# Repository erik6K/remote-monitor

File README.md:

# Repeater Monitor
## Background
An IoT device has been created to monitor the 240V AC normal supply, and 12V DC battery back-up supply for a radio repeater. Refer to the Project Design and Testing Document submitted along with this git repository for more information. The purpose of this git repository is to:
* Store the Arduino firmware backups for deploying new devices, or adding functionality
* Store relevent hardware manuals

To facilitate continuous deployment of the web application, it has been moved to a separate git repository. Updates to the web application should be made within this repository: [Repeater Monitor Web Application](https://github.com/tarrantja/remote-monitor-web). Updates made to the web application contained within this repository will not be deployed. 

## Authors
Created by:
* **Rio Akbar** (22507035)
* **Calvin Nguyen** (22509815)
* **Erik Stefan** (22224939)
* **James Tarrant** (20924309)
* **Dylan Turner** (22240231)

Developed for use in CITS3200, on behalf of SES CSU. 
[The full git repository can be found here.](https://github.com/tarrantja/remote-monitor-web)

## Licences
Hardware: CC BY-NC 3.0 AU

Firmware: GPLv3

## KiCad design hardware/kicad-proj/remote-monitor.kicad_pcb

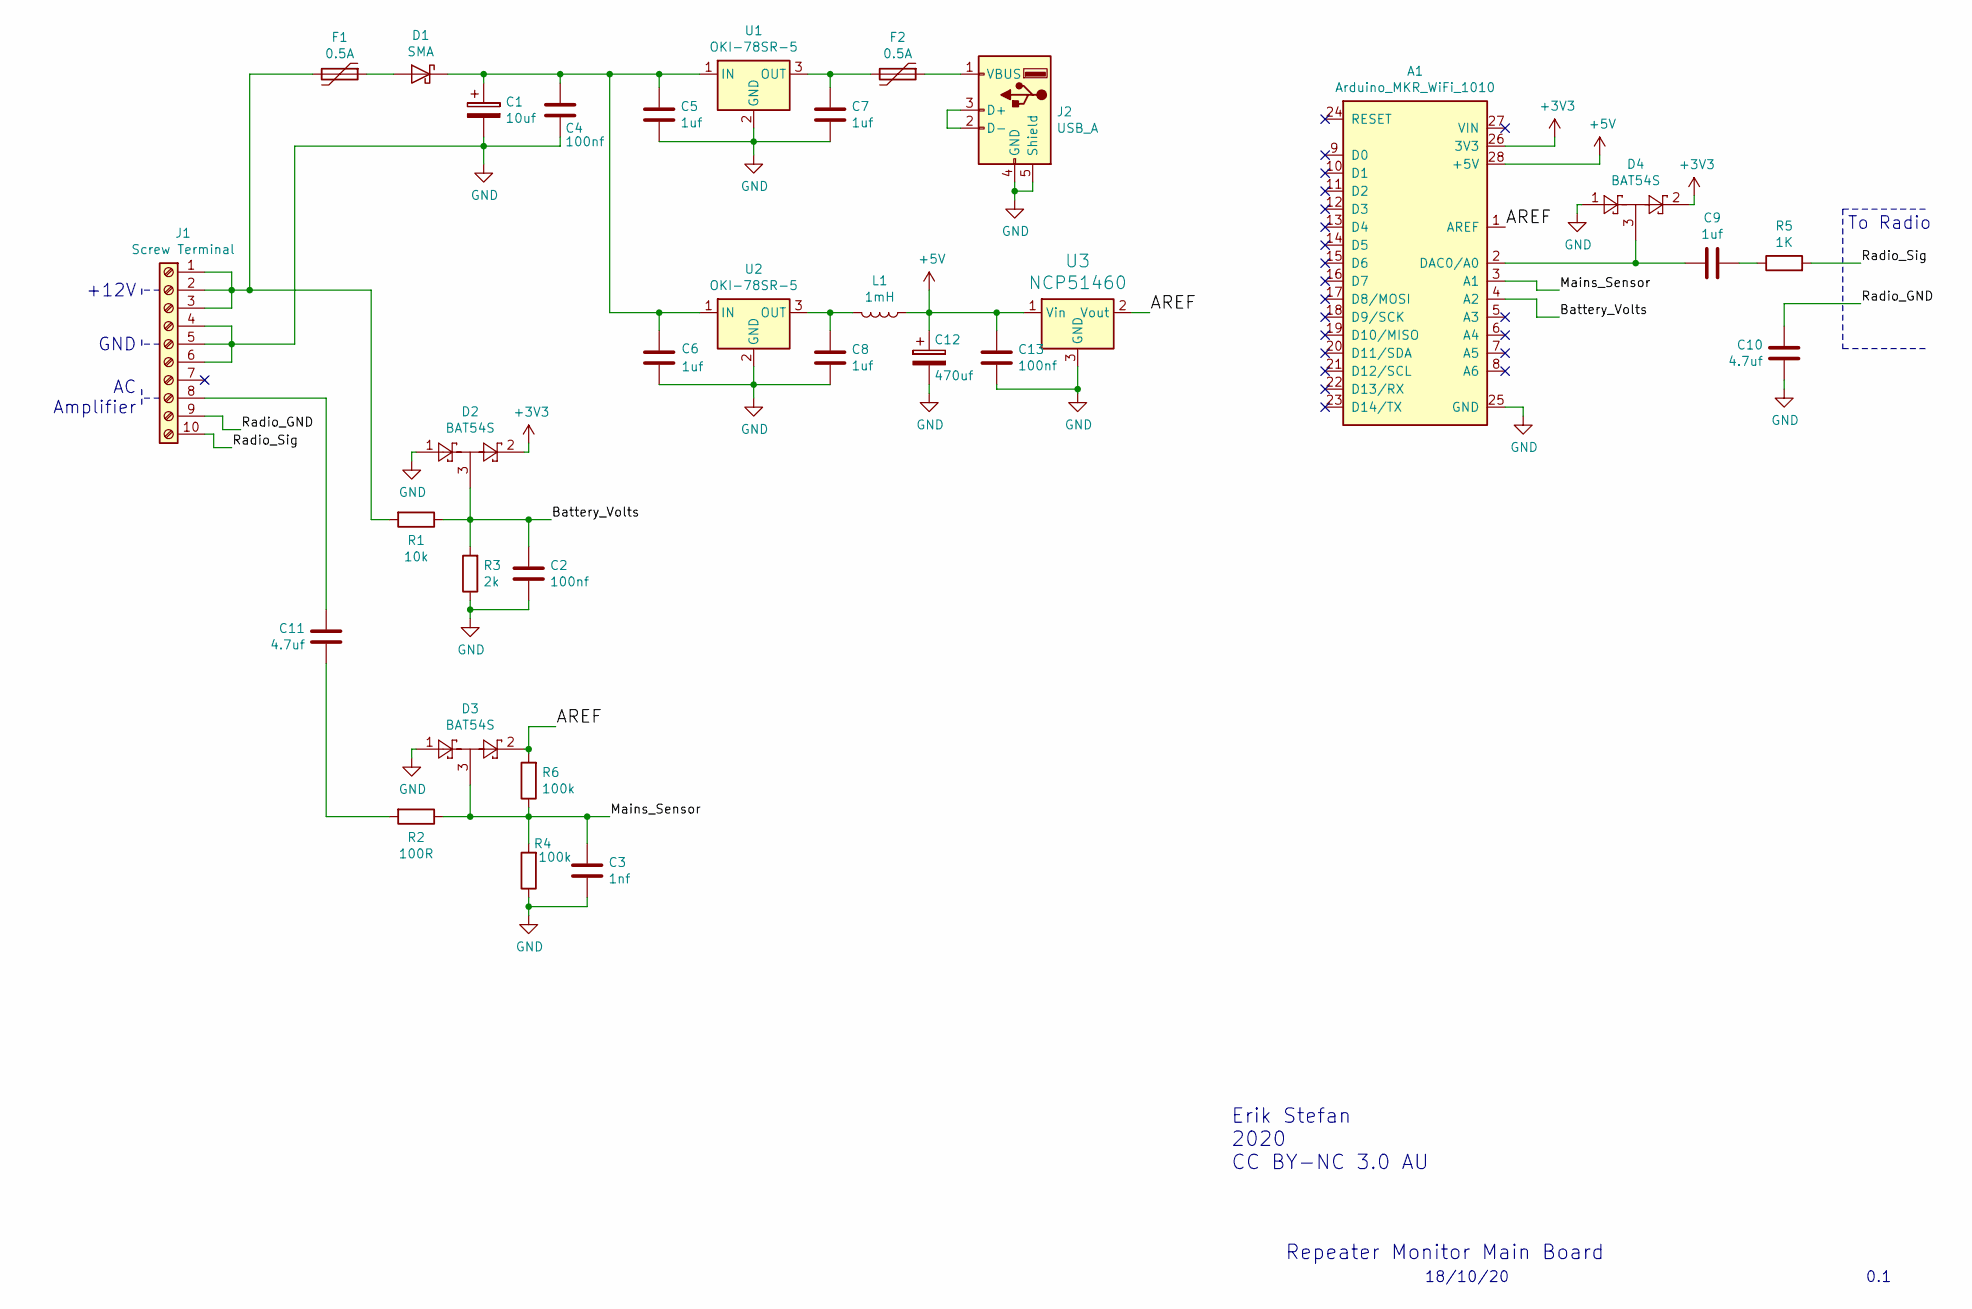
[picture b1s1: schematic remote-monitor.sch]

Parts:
A1: Arduino_MKR_WiFi_1010; Arduino_MKR_1010
C1: 10uf; CP_Elec_5x4.5
C2, C4, C13: 100nf; C_1206_3216Metric
C3: 1nf; C_1206_3216Metric
C5, C6, C7, C8, C9: 1uf; C_1206_3216Metric
C10, C11: 4.7uf; C_1206_3216Metric
C12: 470uf; CP_Elec_8x10.5
D1: SMA; D_SMA
D2, D3, D4: BAT54S; SOT-23
F1, F2: 0.5A; Fuse_1812_4532Metric
J1: Screw Terminal; Screw_Terminal_1x10
J2: USB_A; USB_A_Molex_105057_Vertical
L1: 1mH; L_6.3x6.3_H3
R1: 10k; R_1206_3216Metric
R2: 100R; R_1206_3216Metric
R3: 2k; R_1206_3216Metric
R4, R6: 100k; R_1206_3216Metric
R5: 1K; R_1206_3216Metric
U1, U2: OKI-78SR-5; Converter_DCDC_muRata_OKI-78SR_Vertical
U3: NCP51460; SOT-23

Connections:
+3V3: A1.26 (3V3), D2.2, D4.2
+5V: A1.28 (+5V), C12.1, C13.1, L1.1, U3.1 (Vin)
/AREF: A1.1 (AREF), D3.2, R6.2, U3.2 (Vout)
/Battery_Volts: A1.4 (A2), C2.1, D2.3, R1.1, R3.2
/Mains_Sensor: A1.3 (A1), C3.1, D3.3, R2.1, R4.2, R6.1
/Radio_GND: C10.1, J1.9
/Radio_Sig: J1.10, R5.2
GND: A1.25 (GND), C1.2, C2.2, C3.2, C4.2, C5.2, C6.2, C7.2, C8.2, C10.2, C12.2, C13.2, D2.1, D3.1, D4.1, J1.4, J1.5, J1.6, J2.4 (GND), J2.5 (Shield), R3.1, R4.1, U1.2 (GND), U2.2 (GND), U3.3 (GND)
unnamed: A1.2 (DAC0/A0), C9.2, D4.3
unnamed: C1.1, C4.1, C5.1, C6.1, D1.1 (K), U1.1 (IN), U2.1 (IN)
unnamed: C7.1, F2.2, U1.3 (OUT)
unnamed: C8.1, L1.2, U2.3 (OUT)
unnamed: C9.1, R5.1
unnamed: C11.1, J1.8
unnamed: C11.2, R2.2
unnamed: D1.2 (A), F1.1
unnamed: F1.2, J1.1, J1.2, J1.3, R1.2
unnamed: F2.1, J2.1 (VBUS)
unnamed: J2.2 (D-), J2.3 (D+)

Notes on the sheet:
0.1
Repeater Monitor Main Board
Erik Stefan 2020 CC BY-NC 3.0 AU
18/10/20
+12V
GND
AC Amplifier
To Radio

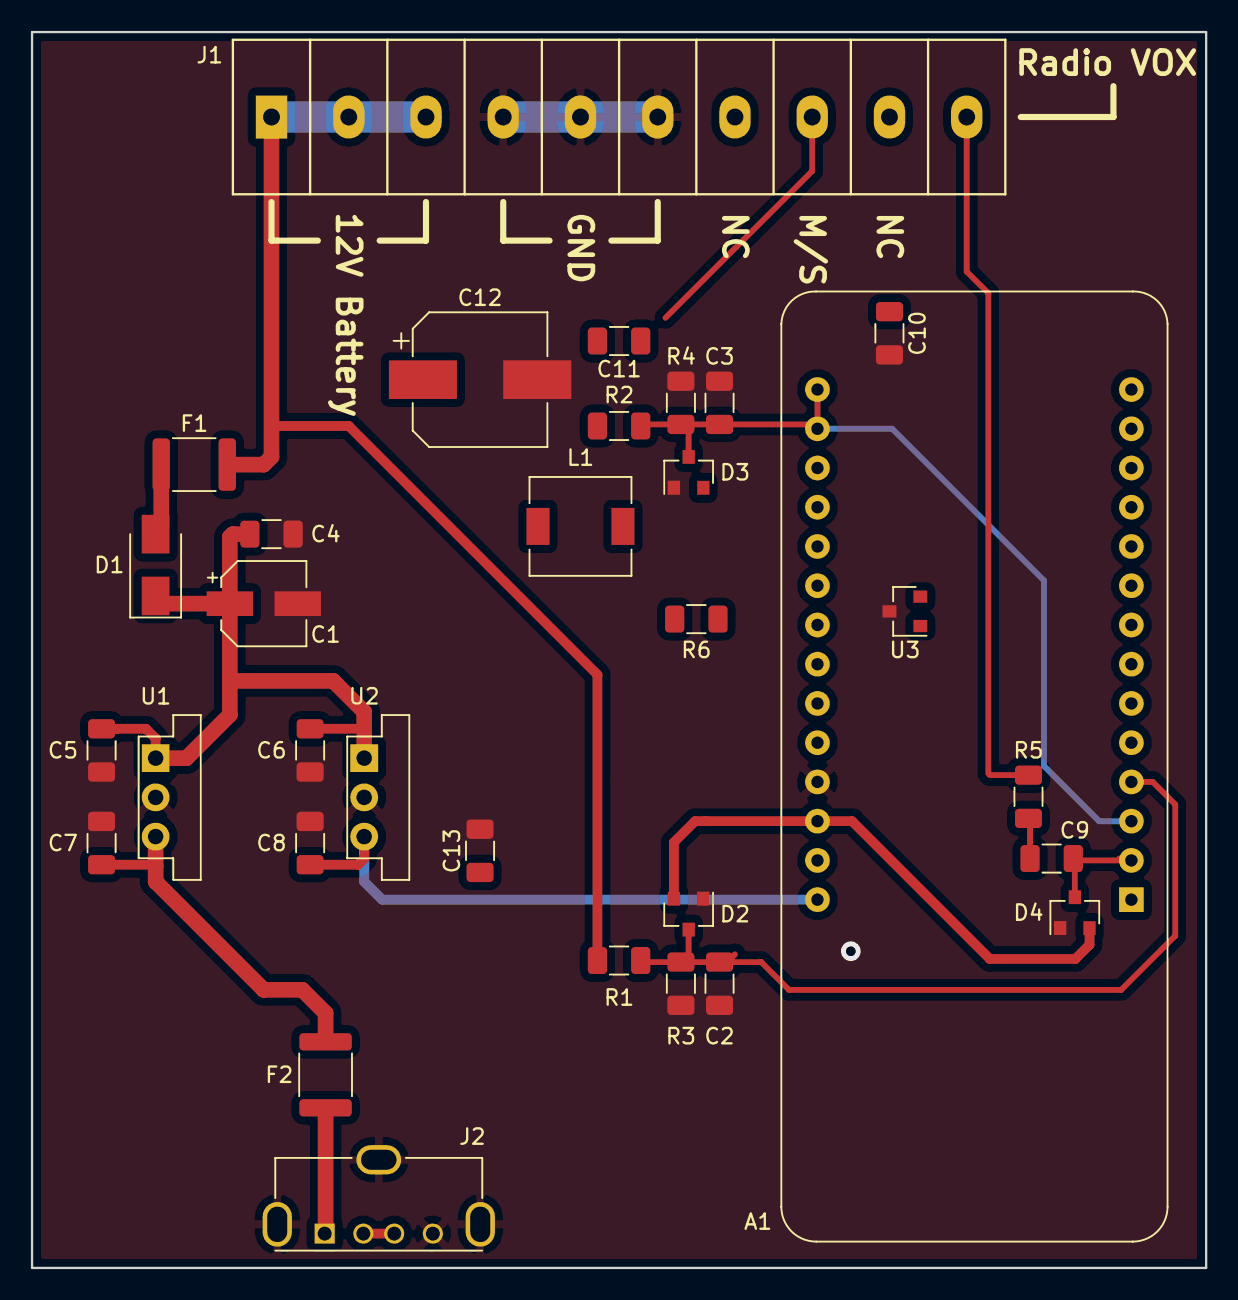
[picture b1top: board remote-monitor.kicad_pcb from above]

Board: 2 copper layers, 76.0 x 80.0 mm, 32 parts (0 on the bottom side), 19 nets.

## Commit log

2020-08-25 added .gitignore for kiCAD
2020-08-25 initial kicad setup and block diagram
2020-08-27 Demo for Arduino cloud
2020-08-27 Added gitignore
2020-08-27 Gitignore
2020-08-28 power supply
2020-08-28 Initial commit for web app
2020-08-28 More updates
2020-08-29 prototype main board complete
2020-08-30 Trialled Arduino Cloud API
2020-08-30 Updated gitignore
2020-08-30 Working AWS Prototype
2020-08-30 Arduino sketch for AWS
2020-08-30 gitignore venv
2020-08-30 Added ENV variable steps to readme
2020-08-30 Untrack files in .gitignore
2020-08-30 updated pcb dimensions and mounting holes for different enclosure
2020-08-30 Launch instructions
2020-08-31 initial firmware structure
2020-08-31 fix error in monitor.cpp
2020-09-03 added timer
2020-09-03 fixed errors
2020-09-03 Firmware update for mains sensor
2020-09-04 compact digital filter
2020-09-06 AWS Beanstalk Trial
2020-09-06 Updated readme for windows
2020-09-08 fix styling for different devices
2020-09-08 test
2020-09-08 Firmware digital filter tweak
2020-09-30 Remove venv
2020-09-30 testing azure
2020-10-01 freerun adc working
2020-10-01 deleted unecessary files
2020-10-02 clean-up and added state machine for swapping ADC between battery and mains sensing
2020-10-02 Read Azure Devices
2020-10-04 FFT working
2020-10-04 adc can now swap between battery and mains sampling
2020-10-04 Live fetching of telemetry
2020-10-05 Deploy to Azure Cloud
2020-10-09 modified FFT function to return magnitude
2020-10-09 some code cleanup
2020-10-11 modifications for auto-gain amplifier
2020-10-12 Azure API
2020-10-12 IoT Cloud Firmware
2020-10-12 comments
2020-10-12 Libraries for IoT Cloud connection
2020-10-12 initial merge of IoT code
2020-10-12 compiling on linux
2020-10-12 ready for testing
2020-10-12 Pycache to gitignore
2020-10-12 Merge
2020-10-13 take out admin
2020-10-13 Moved MQTT Loop
2020-10-13 moved mqqt loop
2020-10-14 rgb led notification
2020-10-14 removed wifi
2020-10-14 fixed mistakes
2020-10-14 testing interrupt disables
2020-10-15 Commenting
2020-10-16 testing GCLK settings causing issues
2020-10-16 possibly removed need for RTC
2020-10-17 reconnection logic
2020-10-17 Mains ON OFF
2020-10-17 averaging mains status
2020-10-17 rm unused files
2020-10-18 Reporting of float value for battery
2020-10-18 License Info Reporter
2020-10-18 NTP Library License
2020-10-18 LED notification, general cleanup, improved battery monitoring
2020-10-19 cleanup
2020-10-19 removed blocking till serial connected
2020-10-19 updated hardware designs
